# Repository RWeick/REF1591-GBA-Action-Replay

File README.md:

# REF1591-GBA-Action-Replay
The Kicad files for the REF1591 GBA Action Replay

PCB Thickness: 0.8 mm

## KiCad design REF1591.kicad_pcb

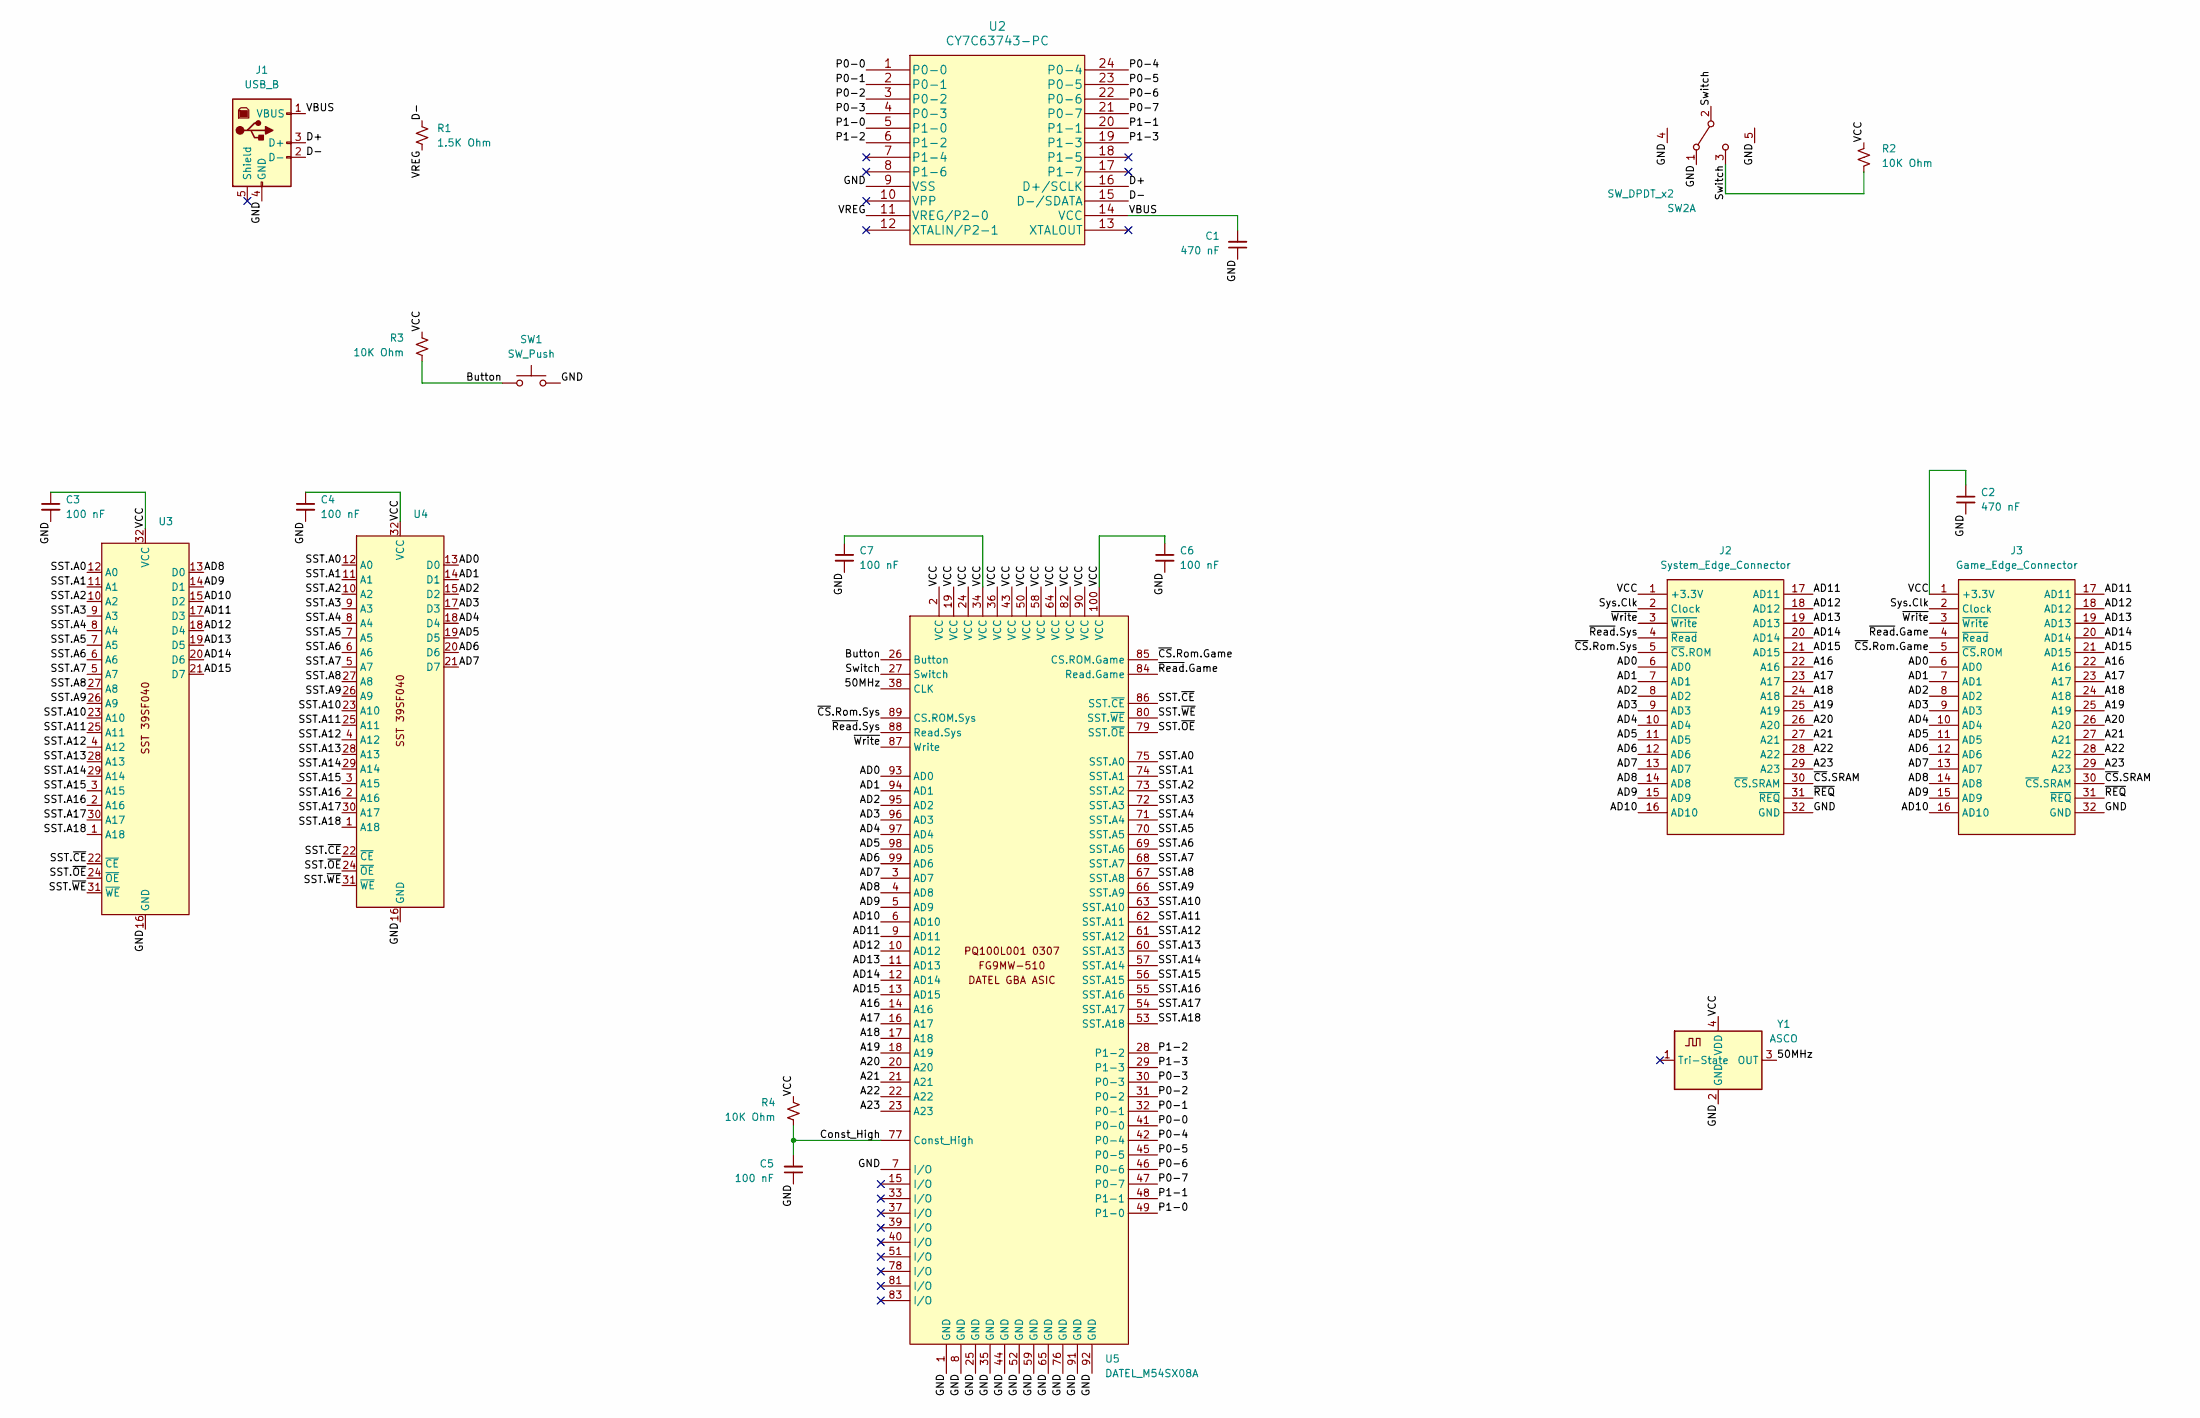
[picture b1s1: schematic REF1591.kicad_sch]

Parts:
C1, C2: 470 nF; SMD Passive
C3, C4, C5, C6, C7: 100 nF; SMD Passive
J1: USB_B; USB_B_OST_USB-B1HSxx_Horizontal
J2: System_Edge_Connector; Edge Connector
J3: Game_Edge_Connector; Cartridge Slot
R1: 1.5K Ohm; SMD Passive
R2, R3, R4: 10K Ohm; SMD Passive
SW1: SW_Push; Button
SW2: SW_DPDT_x2; Switch
U2: CY7C63743-PC; Cypress
U3, U4: PLCC32
U5: DATEL_M54SX08A; FPGA
Y1: ASCO; Crystal

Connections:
/50MHz: U5.38 (CLK), Y1.3 (OUT)
/A16: J2.22 (A16), J3.22 (A16), U5.14 (A16)
/A17: J2.23 (A17), J3.23 (A17), U5.16 (A17)
/A18: J2.24 (A18), J3.24 (A18), U5.17 (A18)
/A19: J2.25 (A19), J3.25 (A19), U5.18 (A19)
/A20: J2.26 (A20), J3.26 (A20), U5.20 (A20)
/A21: J2.27 (A21), J3.27 (A21), U5.21 (A21)
/A22: J2.28 (A22), J3.28 (A22), U5.22 (A22)
/A23: J2.29 (A23), J3.29 (A23), U5.23 (A23)
/AD0: J2.6 (AD0), J3.6 (AD0), U4.13 (D0), U5.93 (AD0)
/AD1: J2.7 (AD1), J3.7 (AD1), U4.14 (D1), U5.94 (AD1)
/AD2: J2.8 (AD2), J3.8 (AD2), U4.15 (D2), U5.95 (AD2)
/AD3: J2.9 (AD3), J3.9 (AD3), U4.17 (D3), U5.96 (AD3)
/AD4: J2.10 (AD4), J3.10 (AD4), U4.18 (D4), U5.97 (AD4)
/AD5: J2.11 (AD5), J3.11 (AD5), U4.19 (D5), U5.98 (AD5)
/AD6: J2.12 (AD6), J3.12 (AD6), U4.20 (D6), U5.99 (AD6)
/AD7: J2.13 (AD7), J3.13 (AD7), U4.21 (D7), U5.3 (AD7)
/AD8: J2.14 (AD8), J3.14 (AD8), U3.13 (D0), U5.4 (AD8)
/AD9: J2.15 (AD9), J3.15 (AD9), U3.14 (D1), U5.5 (AD9)
/AD10: J2.16 (AD10), J3.16 (AD10), U3.15 (D2), U5.6 (AD10)
/AD11: J2.17 (AD11), J3.17 (AD11), U3.17 (D3), U5.9 (AD11)
/AD12: J2.18 (AD12), J3.18 (AD12), U3.18 (D4), U5.10 (AD12)
/AD13: J2.19 (AD13), J3.19 (AD13), U3.19 (D5), U5.11 (AD13)
/AD14: J2.20 (AD14), J3.20 (AD14), U3.20 (D6), U5.12 (AD14)
/AD15: J2.21 (AD15), J3.21 (AD15), U3.21 (D7), U5.13 (AD15)
/Button: R3.1, SW1.1, U5.26 (Button)
/Const_High: C5.2, R4.1, U5.77 (Const_High)
/D+: J1.3 (D+), U2.16 (D+/SCLK)
/D-: J1.2 (D-), R1.1, U2.15 (D-/SDATA)
/GND: C1.1, C2.2, C3.2, C4.2, C5.1, C6.2, C7.2, J1.4 (GND), J2.32 (GND), J3.32 (GND), SW1.2, SW1.3, SW1.4, SW2.1 (A), SW2.4 (Case_GND), SW2.5 (Case_GND), U2.9 (VSS), U3.16 (GND), U4.16 (GND), U5.1 (GND), U5.7 (I/O), U5.8 (GND), U5.25 (GND), U5.35 (GND), U5.44 (GND), U5.52 (GND), U5.59 (GND), U5.65 (GND), U5.76 (GND), U5.91 (GND), U5.92 (GND), Y1.2 (GND)
/P0-0: U2.1 (P0-0), U5.41 (P0-0)
/P0-1: U2.2 (P0-1), U5.32 (P0-1)
/P0-2: U2.3 (P0-2), U5.31 (P0-2)
/P0-3: U2.4 (P0-3), U5.30 (P0-3)
/P0-4: U2.24 (P0-4), U5.42 (P0-4)
/P0-5: U2.23 (P0-5), U5.45 (P0-5)
/P0-6: U2.22 (P0-6), U5.46 (P0-6)
/P0-7: U2.21 (P0-7), U5.47 (P0-7)
/P1-0: U2.5 (P1-0), U5.49 (P1-0)
/P1-1: U2.20 (P1-1), U5.48 (P1-1)
/P1-2: U2.6 (P1-2), U5.28 (P1-2)
/P1-3: U2.19 (P1-3), U5.29 (P1-3)
/SST.A0: U3.12 (A0), U4.12 (A0), U5.75 (SST.A0)
/SST.A1: U3.11 (A1), U4.11 (A1), U5.74 (SST.A1)
/SST.A2: U3.10 (A2), U4.10 (A2), U5.73 (SST.A2)
/SST.A3: U3.9 (A3), U4.9 (A3), U5.72 (SST.A3)
/SST.A4: U3.8 (A4), U4.8 (A4), U5.71 (SST.A4)
/SST.A5: U3.7 (A5), U4.7 (A5), U5.70 (SST.A5)
/SST.A6: U3.6 (A6), U4.6 (A6), U5.69 (SST.A6)
/SST.A7: U3.5 (A7), U4.5 (A7), U5.68 (SST.A7)
/SST.A8: U3.27 (A8), U4.27 (A8), U5.67 (SST.A8)
/SST.A9: U3.26 (A9), U4.26 (A9), U5.66 (SST.A9)
/SST.A10: U3.23 (A10), U4.23 (A10), U5.63 (SST.A10)
/SST.A11: U3.25 (A11), U4.25 (A11), U5.62 (SST.A11)
/SST.A12: U3.4 (A12), U4.4 (A12), U5.61 (SST.A12)
/SST.A13: U3.28 (A13), U4.28 (A13), U5.60 (SST.A13)
/SST.A14: U3.29 (A14), U4.29 (A14), U5.57 (SST.A14)
/SST.A15: U3.3 (A15), U4.3 (A15), U5.56 (SST.A15)
/SST.A16: U3.2 (A16), U4.2 (A16), U5.55 (SST.A16)
/SST.A17: U3.30 (A17), U4.30 (A17), U5.54 (SST.A17)
/SST.A18: U3.1 (A18), U4.1 (A18), U5.53 (SST.A18)
/SST.~CE: U3.22 (~CE), U4.22 (~CE), U5.86 (SST.~CE)
/SST.~OE: U3.24 (~OE), U4.24 (~OE), U5.79 (SST.~OE)
/SST.~WE: U3.31 (~WE), U4.31 (~WE), U5.80 (SST.~WE)
/Switch: R2.1, SW2.2 (B), SW2.3 (C), U5.27 (Switch)
/Sys.Clk: J2.2 (Clock), J3.2 (Clock)
/VBUS: C1.2, J1.1 (VBUS), U2.14 (VCC)
/VCC: C2.1, C3.1, C4.1, C6.1, C7.1, J2.1 (+3.3V), J3.1 (+3.3V), R2.2, R3.2, R4.2, U3.32 (VCC), U4.32 (VCC), U5.2 (VCC), U5.19 (VCC), U5.24 (VCC), U5.34 (VCC), U5.36 (VCC), U5.43 (VCC), U5.50 (VCC), U5.58 (VCC), U5.64 (VCC), U5.82 (VCC), U5.90 (VCC), U5.100 (VCC), Y1.4 (VDD)
/VREG: R1.2, U2.11 (VREG/P2-0)
/~CS.Rom.Game: J3.5 (~CS.ROM), U5.85 (CS.ROM.Game)
/~CS.Rom.Sys: J2.5 (~CS.ROM), U5.89 (CS.ROM.Sys)
/~CS.SRAM: J2.30 (~CS.SRAM), J3.30 (~CS.SRAM)
/~REQ: J2.31 (~REQ), J3.31 (~REQ)
/~Read.Game: J3.4 (~Read), U5.84 (Read.Game)
/~Read.Sys: J2.4 (~Read), U5.88 (Read.Sys)
/~Write: J2.3 (~Write), J3.3 (~Write), U5.87 (Write)

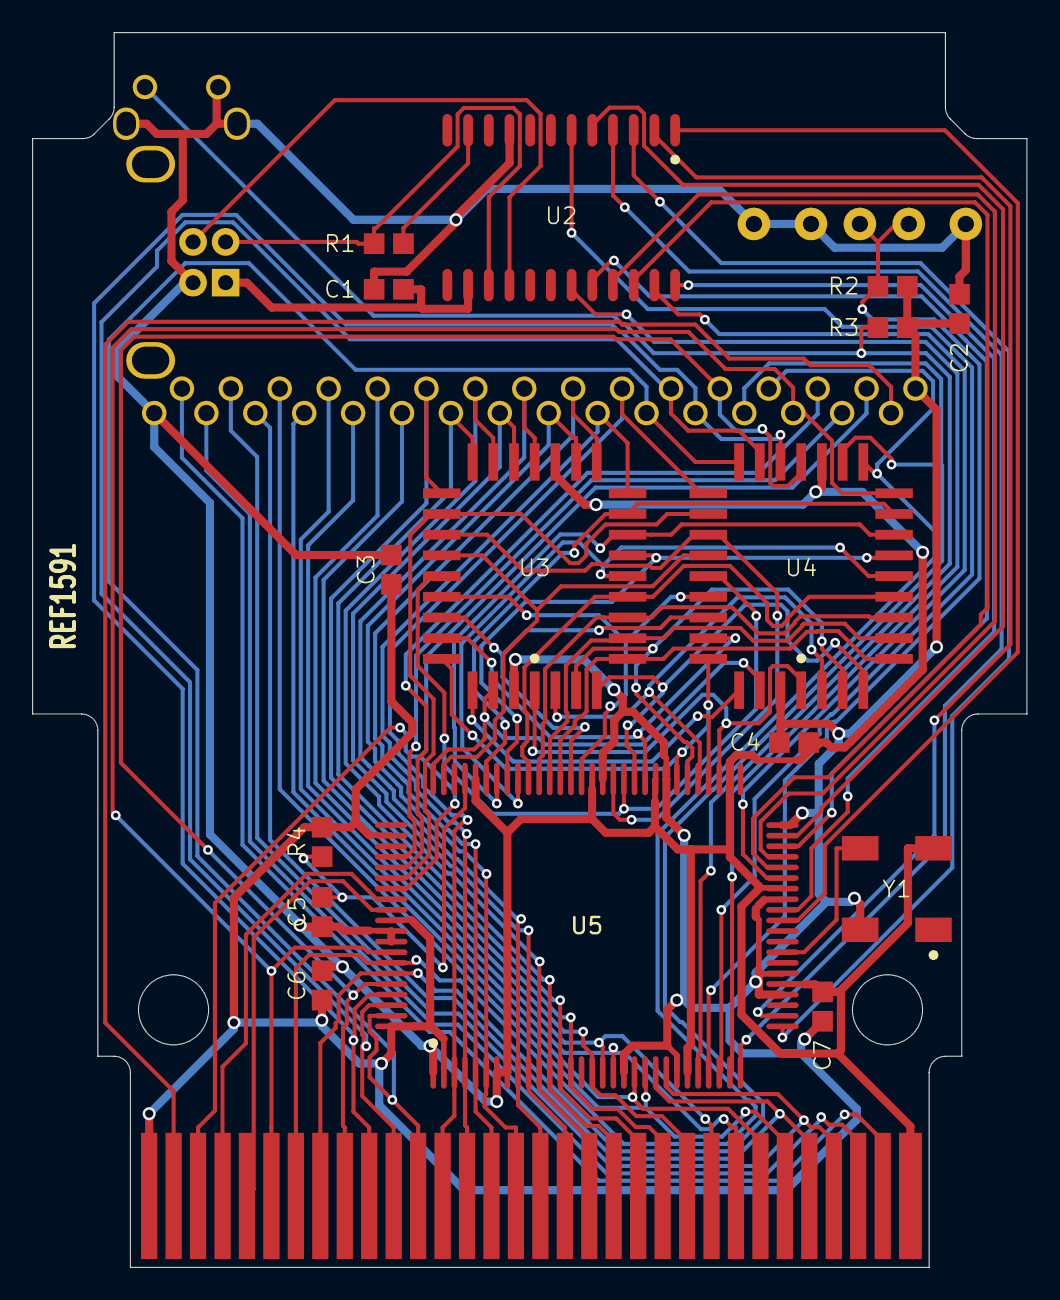
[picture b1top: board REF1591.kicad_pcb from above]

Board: 2 copper layers, 61.0 x 75.8 mm, 21 parts (0 on the bottom side), 76 nets.
